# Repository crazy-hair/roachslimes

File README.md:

# roachslimes

This document is no longer being updated and will only be corrected on major updates! For full documentation please check out [The Docs](https://crazy-hair.github.io/roachslimes/)

A utilitarian tracker design for [SlimeVR](https://docs.slimevr.dev/), with the intention of using the cheapest parts available in the smallest form factor possible, while maintaining quality and usability.

## Ordering PCBs

**NEW!** Revision 2 motherboards have been added, removing the BMI160-QMC5883 IMU-Magnetometer combo, and replacing it with an [LSM6DSR](https://moffshop.deyta.de/products/lsm6dsr) board which has a magnetometer built in. Technically, the LSM6DSR board is pin-compatible with the BMI160 (and therefore is compatible with the old rev 1 boards), but this new design allows for much easier direct mounting (instead of using pin headers) and frees up space for a battery connector, instead of directly soldering the battery to the board. They're currently untested, still waiting for my batch to arrive, so use at your own risk!

The included gerbers in `/PCB/Production/` are exported from KiCad using the recommended settings for [JLCPCB](https://jlcpcb.com). I cannot guarantee that they will work at a different fab. JLCPCB is far and away the most cost effective for low volume PCB orders, coming out to $3.52 for 20 boards before tax if you use their economy shipping option (as of 2024). There are four files, two for each board (one single board, and one panelized). Using the panelized board files is highly recommended, as it allows for More Board Per Board<sup>TM</sup> without additional cost. The default JLCPCB order parameters are good enough for working boards out of the box, but I'd recommend changing the color to yellow [(because it's lemon scented)](https://x.com/MKVRiscy/status/1821870120697987492) and to select "no mark" so you don't have some unique identifier printed on the board somewhere.

## Ordering Parts

Links to all required components can be found in the table futher down.

## Printing Instructions

The print files, STLs, and Fusion source files are included in the `/3D Files/` directory. I highly recommend using the `.3mf` print files as a basis for your print, as there are manually painted supports and custom settings per object (there's one `.3mf` for PrusaSlicer and friends and one for OrcaSlicer and friends).

## Assembly

This board is designed to be compact, which means I had to make some unconventional choices during assembly. The D1 Mini and TP-4056 Boards are mounted to the surface of the PCB, while the BMI and QMC are mounted on headers on the opposite side. For assembly, this means you have to solder the headers on first, then use flush cutters or snips to cut the header pins sticking out of the front of the board down to be flush so you can solder on the boards on the onto the front. There's also a pogo pin header for a future modular charging dock which would allow for charging multiple trackers at once, and a slot for an LED and associated resistor which was added for debugging but can be used to identify trackers if you choose to use different colored LEDs per tracker. The cases are completely toolless and are friction/retention fit. Refer to the animation below for an assembly reference.

## Firmware

Firmware is pretty straightforward, though I did have an issue with the Butterscotch builder/installer - battery sense would always show 100 percent. Therefore, if you want all features to work, I'd recommend building it yourself - PlatformIO Tools for Visual Studio Code make it super easy. If you're compiling yourself, all you have to do is uncomment out `BATTERY_SHIELD_RESISTANCE 180` in `defines.h`, set `USE_6_AXIS false` in `debug.h`, and and change `BMI160_MAG_TYPE BMI160_MAG_TYPE_HMC` to `BMI160_MAG_TYPE BMI160_MAG_TYPE_QMC`in `defines_bmi160.h`. If that makes no sense to you, I've included compiled firmware in the releases section. 

## Price Breakdown

A fully parametric breakdown that allows for adjusting tax, quantity, and more can be found in BOM.xlsx or [here](https://docs.google.com/spreadsheets/d/1RTwIJsGUY1e1f047yFT5OwqJSmgT3SN4hO7gHYImR_g/copy) (if you want to modify it, you'll have to make a copy first).

All prices are in USD. Sales tax is calculated at 8.25%. The table is based on a full set of trackers and includes 2 extra D1s, BMIs, and QMCs to account for possible DOA parts or accidents during assembly. Note that the LED and associated 620Ω resistor, as well as the pogo pins are not necessary for core tracker operation, as specified in the comment row.

| Tracker Components | [D1 Mini v4](https://www.aliexpress.us/item/32831353752.html) | [BMI160](https://www.aliexpress.us/item/1005007143698152.html) | [TP-4056](https://www.aliexpress.us/item/1005006379403615.html) | [GY-271](https://www.aliexpress.us/item/1556804905.html) | [SK12D07VG4](https://www.aliexpress.us/item/3256806149664764.html) | [JST-PH-4P](https://www.aliexpress.us/item/33011797617.html) | [Pogo Female](https://www.aliexpress.us/item/3256804960956555.html) | [B5817WS](https://www.aliexpress.us/item/1005004633629467.html) | [0805 180k](https://www.aliexpress.us/item/1005007032369041.html) | [0806 620r](https://www.aliexpress.us/item/3256806846054289.html) | [0805 LED](https://www.aliexpress.us/item/3256805245629305.html) | [803450](https://www.aliexpress.us/item/1005003621836701.html) | [Wires](https://www.aliexpress.us/item/1005007558078161.html) | Motherboard | Daughterboard | Total |
| ------------------------------ | ---------------------------------------------------------- | -------------------------------------------------------------- | -------------------------------------------------------------- | -------------------------------------------------------- | ------------------------------------------------------------------ | ------------------------------------------------------------ | ------------------------------------------------------------------- | --------------------------------------------------------------- | ----------------------------------------------------------------- | ----------------------------------------------------------------- | ---------------------------------------------------------------- | -------------------------------------------------------------- | ------------------------------------------------------------- | ----------------------------- | --------------------------------- | ------------ |
| Listing Price | $1.43 | $0.88 | $3.27 | $0.58 | $1.20 | $3.79 | $12.93 | $1.20 | $1.05 | $1.05 | $2.47 | $25.99 | $11.93 | $2.00 | $2.00 | |
| Shipping | $2.63 | $2.32 | $ \- | $ \- | $ \- | $ \- | $ \- | $ \- | $ \- | $ \- | $ \- | $ \- | $ \- | $1.52 | $1.52 | $7.99 |
| Subtotal | $15.50 | $12.88 | $3.27 | $6.96 | $1.20 | $3.79 | $12.93 | $1.20 | $1.05 | $1.05 | $2.47 | $25.99 | $11.93 | $3.52 | $3.52 | $107.26 |
| Tax | $1.28 | $1.06 | $0.27 | $0.57 | $0.10 | $0.31 | $1.07 | $0.10 | $0.09 | $0.09 | $0.20 | $2.14 | $0.98 | $0.29 | $0.29 | $8.85 |
| Total | $16.78 | $13.94 | $3.54 | $7.53 | $1.30 | $4.10 | $14.00 | $1.30 | $1.14 | $1.14 | $2.67 | $28.13 | $12.91 | $3.81 | $3.81 | $116.11 |
| Order Quantity | 9 | 12 | 1 | 12 | 1 | 1 | 1 | 1 | 1 | 1 | 1 | 1 | 1 | 1 | 1 | |
| Item Quantity | 1 | 1 | 20 | 1 | 20 | 100 | 20 | 100 | 100 | 100 | 600 | 10 | 12 | 20 | 40 | |
| Price Per Unit | $1.86 | $1.16 | $0.18 | $0.63 | $0.06 | $0.04 | $0.70 | $0.01 | $0.01 | $0.01 | $0.00 | $2.81 | $1.08 | $0.19 | $0.10 | |
| | | | | | | | | | | | | | | | | |
| Quantity Per Primary Tracker | 1 | 1 | 1 | 1 | 1 | 1 | 1 | 2 | 1 | 1 | 1 | 1 | 0 | 1 | 0 | |
| Quantity Per Secondary Tracker | 0 | 1 | 0 | 1 | 0 | 1 | 0 | 0 | 0 | 0 | 0 | 0 | 1 | 0 | 1 | |
| | | | | | | | | | | | | | | | | |
| Price Per Primary Tracker | $1.86 | $1.16 | $0.18 | $0.63 | $0.06 | $0.04 | $0.70 | $0.03 | $0.01 | $0.01 | $0.00 | $2.81 | $ \- | $0.19 | $ \- | $7.69 |
| Price Per Secondary Tracker | $ \- | $1.16 | $ \- | $0.63 | $ \- | $0.04 | $ \- | $ \- | $ \- | $ \- | $ \- | $ \- | $1.08 | $ \- | $0.10 | $3.00 |
| | | | | | | | | | | | | | | | | |
| Comment | | | | | | | Optional | | | Optional | Optional | | | | | |

## Gallery

## Credits

List of models used:

| Model | Credit |
|--|--:|
| Wemos D1 Mini v4 | [FBMinis](https://grabcad.com/library/wemos-esp8266-lolin-d1-mini-v4-1) |
| TP-4056 | [Babu George](https://grabcad.com/library/03962a-hw107-lithium-battery-charging-module-1) |
| BMI160 | [Kouno](https://store.kouno.xyz/products/bmi270-breakout-board) |
| GY-271 | [Benas Griauzde](https://grabcad.com/library/gy-271-hmc5883l-triple-3-axis-digital-compass-magnetometer-sensor-module-1) |

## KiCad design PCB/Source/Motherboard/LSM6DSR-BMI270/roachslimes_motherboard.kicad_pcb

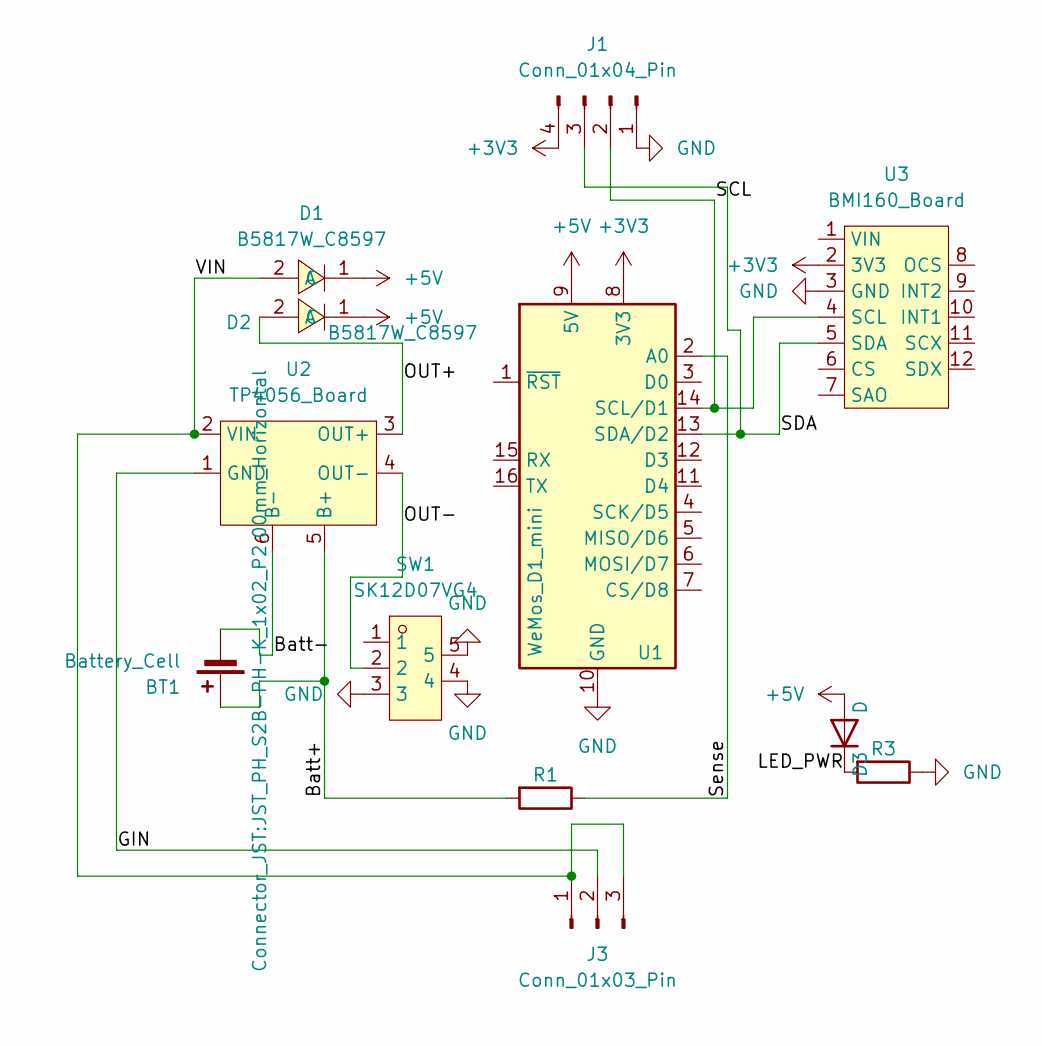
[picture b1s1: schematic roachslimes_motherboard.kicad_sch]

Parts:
BT1: Battery_Cell; JST_PH_S2B-PH-K_1x02_P2.00mm_Horizontal
D1, D2: B5817W_C8597; SOD-123_L2.8-W1.8-LS3.7-RD_custom; LCSC Part C8597
D3: D; LED_0805_2012Metric_Pad1.15x1.40mm_HandSolder
J1: Conn_01x04_Pin; JST_PH_S4B-PH-K_1x04_P2.00mm_Horizontal_labelled_1
J3: Conn_01x03_Pin; pogo_3_pin_right_angle
R1, R3: R; R_0805_2012Metric_Pad1.20x1.40mm_HandSolder
SW1: SK12D07VG4; SW-TH_SK12D07VG4_custom; LCSC Part C2887263
U1: WeMos_D1_mini; WEMOS_D1_mini_light_labeled_both_sides_1
U2: TP4056_Board; TP4056_both_sides_1
U3: BMI160_Board; LSM6DSR _Board

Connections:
+3V3: J1.4, U1.8 (3V3), U3.2 (3V3)
+5V: D1.1 (C), D2.1 (C), D3.2 (A), U1.9 (5V)
/Batt+: BT1.1 (+), R1.2, U2.5 (B+)
/Batt-: BT1.2 (-), U2.6 (B-)
/GIN: J3.2, U2.1 (GND)
/LED_PWR: D3.1 (K), R3.2
/OUT+: D2.2 (A), U2.3 (OUT+)
/OUT-: SW1.2, U2.4 (OUT-)
/SCL: J1.2, U1.14 (SCL/D1), U3.4 (SCL)
/SDA: J1.3, U1.13 (SDA/D2), U3.5 (SDA)
/Sense: R1.1, U1.2 (A0)
/VIN: D1.2 (A), J3.1, J3.3, U2.2 (VIN)
GND: J1.1, R3.1, SW1.3, SW1.4, SW1.5, U1.10 (GND), U3.3 (GND)

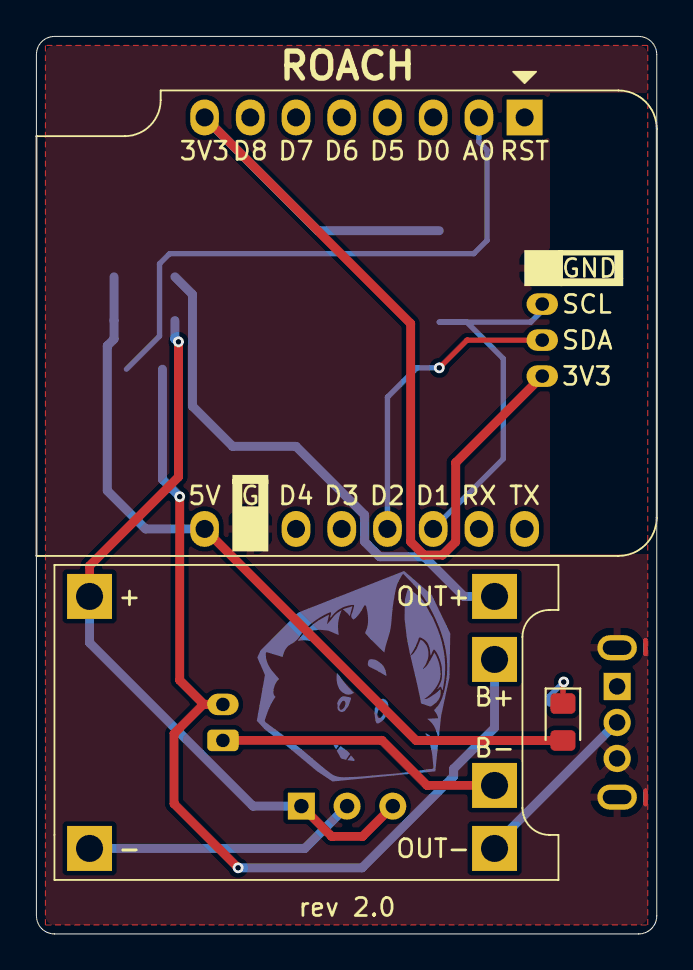
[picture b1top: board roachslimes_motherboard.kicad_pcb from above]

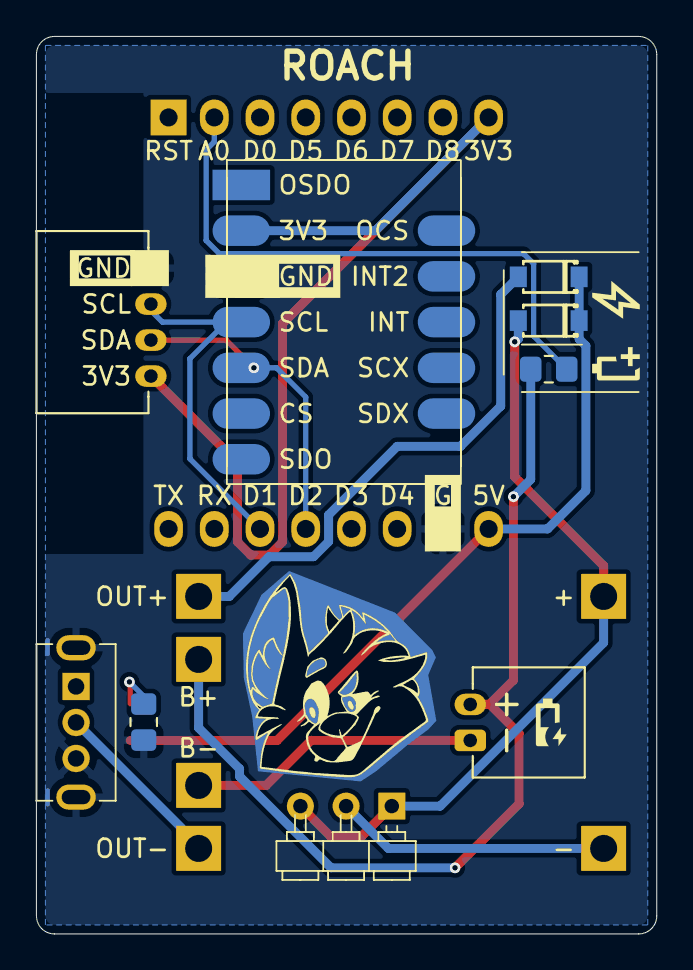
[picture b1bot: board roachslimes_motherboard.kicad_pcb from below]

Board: 2 copper layers, 34.5 x 49.9 mm, 12 parts (9 on the bottom side), 13 nets.

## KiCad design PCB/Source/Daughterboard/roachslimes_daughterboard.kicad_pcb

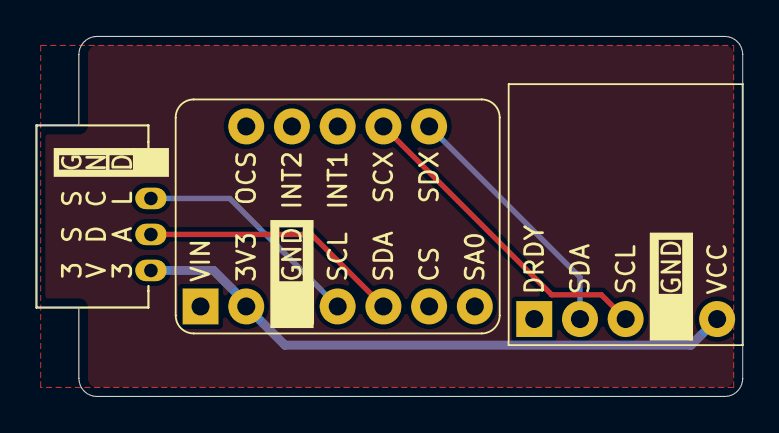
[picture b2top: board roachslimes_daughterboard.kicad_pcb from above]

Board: 2 copper layers, 39.2 x 20.0 mm, 3 parts (0 on the bottom side), 6 nets.

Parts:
J1: JST PH 4p; JST_PH_1x4_labelled
U1: BMI160; BMI160_Board_both_sides_1
U2: GY-271; GY-271_both_sides_1

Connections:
+3V3: J1.4, U1.2 (3V3), U2.5 (VCC)
/SCL: J1.2, U1.4 (SCL)
/SCX: U1.11 (SCX), U2.3 (SCL)
/SDA: J1.3, U1.5 (SDA)
/SDX: U1.12 (SDX), U2.2 (SDA)
GND: J1.1, U1.3 (GND), U2.4 (GND)

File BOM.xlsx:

Tracker Components | D1 Mini | BMI160 | TP4056 | GY-271 | SK12D07VG4 | JST-PH-4P | Pogo Female | B5817WS | 0805 180k | 0806 620r | 0805 LED | 803450 | Wires | Motherboard | Daughterboard | Total
Listing Price | 1.43 | 0.88 | 3.27 | 0.57999999999999996 | 1.2 | 3.79 | 12.93 | 1.2 | 1.05 | 1.05 | 2.4700000000000002 | 25.99 | 11.93 | 2 | 2
Shipping | 2.63 | 2.3199999999999998 | 0 | 0 | 0 | 0 | 0 | 0 | 0 | 0 | 0 | 0 | 0 | 1.52 | 1.52 | 7.9899999999999984
Subtotal | 15.5 | 12.88 | 3.27 | 6.9599999999999991 | 1.2 | 3.79 | 12.93 | 1.2 | 1.05 | 1.05 | 2.4700000000000002 | 25.99 | 11.93 | 3.52 | 3.52 | 107.25999999999999 |  | Tax Rate
Tax | 1.2787500000000001 | 1.0626000000000002 | 0.26977499999999999 | 0.57419999999999993 | 9.9000000000000005E-2 | 0.31267500000000004 | 1.0667249999999999 | 9.9000000000000005E-2 | 8.6625000000000008E-2 | 8.6625000000000008E-2 | 0.20377500000000004 | 2.1441750000000002 | 0.98422500000000002 | 0.29039999999999999 | 0.29039999999999999 | 8.8489500000000003 |  | 8.2500000000000004E-2
Total | 16.778749999999999 | 13.942600000000001 | 3.5397750000000001 | 7.5341999999999993 | 1.2989999999999999 | 4.1026749999999996 | 13.996725 | 1.2989999999999999 | 1.136625 | 1.136625 | 2.673775 | 28.134174999999999 | 12.914225 | 3.8104 | 3.8104 | 116.10895000000001
Order Quantity | 9 | 12 | 1 | 12 | 1 | 1 | 1 | 1 | 1 | 1 | 1 | 1 | 1 | 1 | 1 |  |  | Materials Cost | Lower Body Set | Core Set | Enhanced Core Set | Full Body Set | Deluxe Tracker Set
Item Quantity | 1 | 1 | 20 | 1 | 20 | 100 | 20 | 100 | 100 | 100 | 600 | 10 | 12 | 20 | 40 |  |  | Primary Tracker Quantity | 5 | 5 | 5 | 7 | 10
Price Per Unit | 1.8643055555555554 | 1.1618833333333334 | 0.17698875 | 0.62784999999999991 | 6.4949999999999994E-2 | 4.1026749999999994E-2 | 0.69983624999999994 | 1.299E-2 | 1.136625E-2 | 1.136625E-2 | 4.4562916666666666E-3 | 2.8134174999999999 | 1.0761854166666667 | 0.19051999999999999 | 9.5259999999999997E-2 |  |  | Secondary Tracker Quantity | 0 | 1 | 3 | 3 | 6 |  | Assembly Time Per Primary Tracker | 33
 |  |  |  |  |  |  |  |  |  |  |  |  |  |  |  |  |  |  |  |  |  |  |  |  | Assembly Time Per Secondary Tracker | 5
Quantity Per Primary Tracker | 1 | 1 | 1 | 1 | 1 | 1 | 1 | 2 | 1 | 1 | 1 | 1 | 0 | 1 | 0 |  |  | 500mm Strap Quantity | 6 | 8 | 8 | 10 | 10 |  | Assembly Time Per Charging Dock | 30
Quantity Per Secondary Tracker | 0 | 1 | 0 | 1 | 0 | 1 | 0 | 0 | 0 | 0 | 0 | 0 | 1 | 0 | 1 |  |  | 300mm Strap Quantity | 0 | 0 | 2 | 2 | 2
 |  |  |  |  |  |  |  |  |  |  |  |  |  |  |  |  |  |  |  |  |  |  |  |  | Hourly Wage | 22
Price Per Primary Tracker | 1.8643055555555554 | 1.1618833333333334 | 0.17698875 | 0.62784999999999991 | 6.4949999999999994E-2 | 4.1026749999999994E-2 | 0.69983624999999994 | 2.598E-2 | 1.136625E-2 | 1.136625E-2 | 4.4562916666666666E-3 | 2.8134174999999999 | 0 | 0.19051999999999999 | 0 | 7.6939469305555557 |  | Price of Primary Trackers | 38.469734652777781 | 38.469734652777781 | 38.469734652777781 | 53.857628513888891 | 76.939469305555562
Price Per Secondary Tracker | 0 | 1.1618833333333334 | 0 | 0.62784999999999991 | 0 | 4.1026749999999994E-2 | 0 | 0 | 0 | 0 | 0 | 0 | 1.0761854166666667 | 0 | 9.5259999999999997E-2 | 3.0022055000000001 |  | Price of Secondary Trackers | 0 | 3.0022055000000001 | 9.0066164999999998 | 9.0066164999999998 | 18.013233
Comment |  |  |  |  |  |  | Optional |  |  | Optional | Optional |  |  |  |  |  |  | Price of 500mm Straps | 4.7803199999999997 | 6.3737599999999999 | 6.3737599999999999 | 7.9672000000000001 | 7.9672000000000001
 |  |  |  |  |  |  |  |  |  |  |  |  |  |  |  |  |  | Price of 300mm Straps | 0 | 0 | 1.32498 | 1.32498 | 1.32498
Ancillary Components | 38x300mm Strap | 38x500mm Strap | Chest Harness
Listing Price | 3.06 | 3.68 | 8.0500000000000007 |  |  |  |  |  |  |  |  |  |  |  |  |  |  | Total Price of Set | 43.250054652777777 | 47.845700152777781 | 55.175091152777782 | 72.156425013888892 | 104.24488230555556
Shipping | 0 | 0 | 0
Subtotal | 6.12 | 7.36 | 8.0500000000000007 |  |  |  |  |  |  |  |  |  |  |  |  |  |  | Assembly Cost | Lower Body Set | Core Set | Enhanced Core Set | Full Body Set | Deluxe Tracker Set
Tax | 0.50490000000000002 | 0.60720000000000007 | 0.66412500000000008 |  |  |  |  |  |  |  |  |  |  |  |  |  |  | Total Price of Primary Assembly | 60.5 | 60.5 | 60.5 | 84.7 | 121
Total | 6.6249000000000002 | 7.9672000000000001 | 8.714125000000001 |  |  |  |  |  |  |  |  |  |  |  |  |  |  | Total Price of Secondary Assembly | 0 | 1.8333333333333333 | 5.5 | 5.5 | 11
Order Quantity | 2 | 2 | 1 |  |  |  |  |  |  |  |  |  |  |  |  |  |  | Total Price of Assembly | 60.5 | 62.333333333333336 | 66 | 90.2 | 132
Item Quantity | 5 | 5 | 1
Price Per Unit | 0.66249000000000002 | 0.79671999999999998 | 8.714125000000001 |  |  |  |  |  |  |  |  |  |  |  |  |  |  | Total Price of Assembled Set | 103.75005465277778 | 110.17903348611111 | 121.17509115277778 | 162.3564250138889 | 236.24488230555556
Comment |  |  | Optional |  |  |  |  |  |  |  |  |  |  |  |  |  |  | Optional Addons | Lower Body Set | Core Set | Enhanced Core Set | Full Body Set | Deluxe Tracker Set
 |  |  |  |  |  |  |  |  |  |  |  |  |  |  |  |  | 0 | Chest Harness | 0 | 0 | 0 | 0 | 0
Charging Dock Components | Pogo Male | USB-C Female SMD | PCB | Total |  |  |  |  |  |  |  |  |  |  |  |  | 0 | Charging Dock | 0 | 0 | 0 | 0 | 0
Listing Price | 2.83 | 1.43 | 2 | 6.26 |  |  |  |  |  |  |  |  |  |  |  |  | 0 | Identity LEDs | 0 | 0 | 0 | 0 | 0
Shipping | 0 | 0 | 1.52 | 1.52 |  |  |  |  |  |  |  |  |  |  |  |  | 1 | 3D Printed Motherboard Cases | 8.4499999999999993 | 8.4499999999999993 | 8.4499999999999993 | 11.83 | 16.899999999999999
Subtotal | 11.32 | 1.43 | 3.52 | 16.27 |  |  |  |  |  |  |  |  |  |  |  |  | 1 | 3D Printed Daughterboard Cases | 0 | 0.83 | 2.4899999999999998 | 2.4899999999999998 | 4.9799999999999995
Tax | 0.93390000000000006 | 0.117975 | 0.29039999999999999 | 1.3422750000000001
Total | 12.2539 | 1.5479749999999999 | 3.8104 | 17.612275 |  |  |  |  |  |  |  |  |  |  |  |  |  | Total Price of Addons | 8.4499999999999993 | 9.2799999999999994 | 10.94 | 14.32 | 21.88
Order Quantity | 4 | 1 | 1
Item Quantity | 5 | 10 | 5 |  |  |  |  |  |  |  |  |  |  |  |  |  |  | Total Price | 112.20005465277778 | 119.45903348611111 | 132.11509115277778 | 176.67642501388889 | 258.12488230555556
Price Per Unit | 0.61269499999999999 | 0.15479749999999998 | 0.76207999999999998
Quantity Per Dock | 8 | 1 | 2
 |  |  |  |  |  | Assembled Price
Price Per Dock | 4.9015599999999999 | 0.15479749999999998 | 1.52416 | 6.5805175 |  | 18.680517500000001
Comment

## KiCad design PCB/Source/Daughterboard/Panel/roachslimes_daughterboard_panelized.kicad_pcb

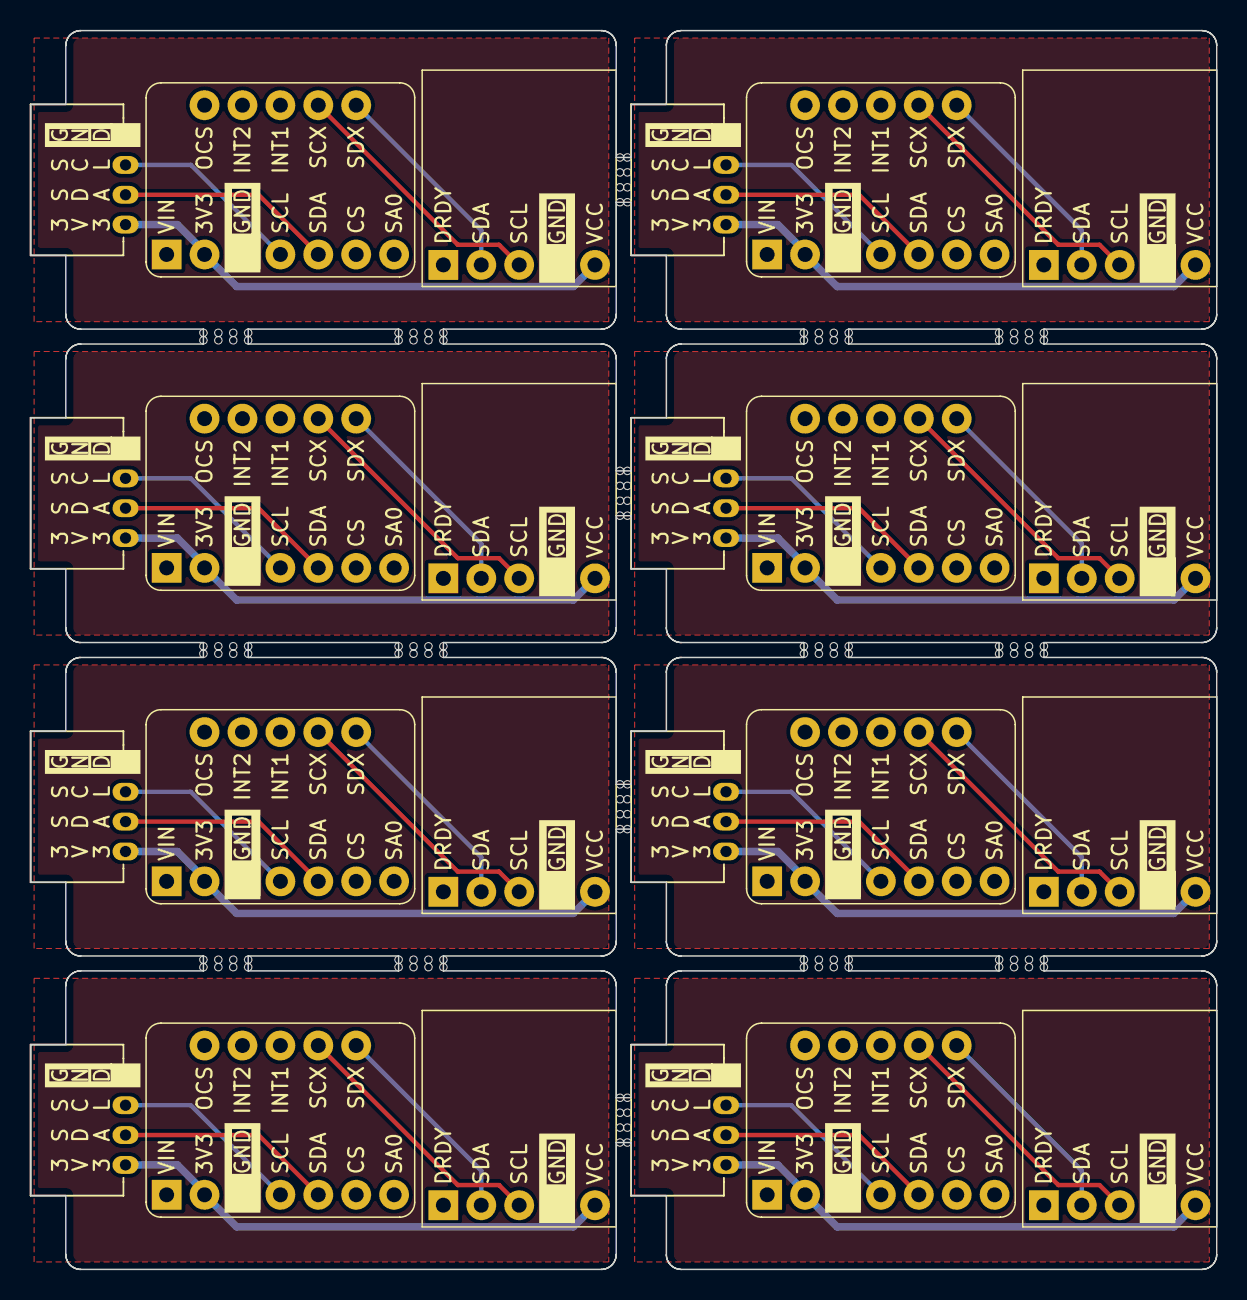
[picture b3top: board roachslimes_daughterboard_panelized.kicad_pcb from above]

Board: 2 copper layers, 79.5 x 83.0 mm, 152 parts (0 on the bottom side), 48 nets.

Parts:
J1, J1#2, J1#3, J1#4, J1#5, J1#6, J1#7, J1#8: JST PH 4p; JST_PH_1x4_labelled
KiKit_MB_1_1, KiKit_MB_1_2, KiKit_MB_1_3, KiKit_MB_1_4, KiKit_MB_2_1, KiKit_MB_2_2, KiKit_MB_2_3, KiKit_MB_2_4, KiKit_MB_3_1, KiKit_MB_3_2, KiKit_MB_3_3, KiKit_MB_3_4, KiKit_MB_4_1, KiKit_MB_4_2, KiKit_MB_4_3, KiKit_MB_4_4, KiKit_MB_5_1, KiKit_MB_5_2, KiKit_MB_5_3, KiKit_MB_5_4, KiKit_MB_6_1, KiKit_MB_6_2, KiKit_MB_6_3, KiKit_MB_6_4, KiKit_MB_7_1, KiKit_MB_7_2, KiKit_MB_7_3, KiKit_MB_7_4, KiKit_MB_8_1, KiKit_MB_8_2, KiKit_MB_8_3, KiKit_MB_8_4, KiKit_MB_9_1, KiKit_MB_9_2, KiKit_MB_9_3, KiKit_MB_9_4, KiKit_MB_10_1, KiKit_MB_10_2, KiKit_MB_10_3, KiKit_MB_10_4, KiKit_MB_11_1, KiKit_MB_11_2, KiKit_MB_11_3, KiKit_MB_11_4, KiKit_MB_12_1, KiKit_MB_12_2, KiKit_MB_12_3, KiKit_MB_12_4, KiKit_MB_13_1, KiKit_MB_13_2, KiKit_MB_13_3, KiKit_MB_13_4, KiKit_MB_14_1, KiKit_MB_14_2, KiKit_MB_14_3, KiKit_MB_14_4, KiKit_MB_15_1, KiKit_MB_15_2, KiKit_MB_15_3, KiKit_MB_15_4, KiKit_MB_16_1, KiKit_MB_16_2, KiKit_MB_16_3, KiKit_MB_16_4, KiKit_MB_17_1, KiKit_MB_17_2, KiKit_MB_17_3, KiKit_MB_17_4, KiKit_MB_18_1, KiKit_MB_18_2, KiKit_MB_18_3, KiKit_MB_18_4, KiKit_MB_19_1, KiKit_MB_19_2, KiKit_MB_19_3, KiKit_MB_19_4, KiKit_MB_20_1, KiKit_MB_20_2, KiKit_MB_20_3, KiKit_MB_20_4, KiKit_MB_21_1, KiKit_MB_21_2, KiKit_MB_21_3, KiKit_MB_21_4, KiKit_MB_22_1, KiKit_MB_22_2, KiKit_MB_22_3, KiKit_MB_22_4, KiKit_MB_23_1, KiKit_MB_23_2, KiKit_MB_23_3, KiKit_MB_23_4, KiKit_MB_24_1, KiKit_MB_24_2, KiKit_MB_24_3, KiKit_MB_24_4, KiKit_MB_25_1, KiKit_MB_25_2, KiKit_MB_25_3, KiKit_MB_25_4, KiKit_MB_26_1, KiKit_MB_26_2, KiKit_MB_26_3, KiKit_MB_26_4, KiKit_MB_27_1, KiKit_MB_27_2, KiKit_MB_27_3, KiKit_MB_27_4, KiKit_MB_28_1, KiKit_MB_28_2, KiKit_MB_28_3, KiKit_MB_28_4, KiKit_MB_29_1, KiKit_MB_29_2, KiKit_MB_29_3, KiKit_MB_29_4, KiKit_MB_30_1, KiKit_MB_30_2, KiKit_MB_30_3, KiKit_MB_30_4, KiKit_MB_31_1, KiKit_MB_31_2, KiKit_MB_31_3, KiKit_MB_31_4, KiKit_MB_32_1, KiKit_MB_32_2, KiKit_MB_32_3, KiKit_MB_32_4: NPTH
U1, U1#2, U1#3, U1#4, U1#5, U1#6, U1#7, U1#8: BMI160; BMI160_Board_both_sides_1
U2, U2#2, U2#3, U2#4, U2#5, U2#6, U2#7, U2#8: GY-271; GY-271_both_sides_1

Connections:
Board_0-+3V3: J1#5.4, U1#7.2 (3V3), U2#7.5 (VCC)
Board_0-/SCL: J1#5.2, U1#7.4 (SCL)
Board_0-/SCX: U1#7.11 (SCX), U2#7.3 (SCL)
Board_0-/SDA: J1#5.3, U1#7.5 (SDA)
Board_0-/SDX: U1#7.12 (SDX), U2#7.2 (SDA)
Board_0-GND: J1#5.1, U1#7.3 (GND), U2#7.4 (GND)
Board_1-+3V3: J1#4.4, U1#3.2 (3V3), U2.5 (VCC)
Board_1-/SCL: J1#4.2, U1#3.4 (SCL)
Board_1-/SCX: U1#3.11 (SCX), U2.3 (SCL)
Board_1-/SDA: J1#4.3, U1#3.5 (SDA)
Board_1-/SDX: U1#3.12 (SDX), U2.2 (SDA)
Board_1-GND: J1#4.1, U1#3.3 (GND), U2.4 (GND)
Board_2-+3V3: J1#7.4, U1#6.2 (3V3), U2#8.5 (VCC)
Board_2-/SCL: J1#7.2, U1#6.4 (SCL)
Board_2-/SCX: U1#6.11 (SCX), U2#8.3 (SCL)
Board_2-/SDA: J1#7.3, U1#6.5 (SDA)
Board_2-/SDX: U1#6.12 (SDX), U2#8.2 (SDA)
Board_2-GND: J1#7.1, U1#6.3 (GND), U2#8.4 (GND)
Board_3-+3V3: J1#3.4, U1.2 (3V3), U2#4.5 (VCC)
Board_3-/SCL: J1#3.2, U1.4 (SCL)
Board_3-/SCX: U1.11 (SCX), U2#4.3 (SCL)
Board_3-/SDA: J1#3.3, U1.5 (SDA)
Board_3-/SDX: U1.12 (SDX), U2#4.2 (SDA)
Board_3-GND: J1#3.1, U1.3 (GND), U2#4.4 (GND)
Board_4-+3V3: J1.4, U1#5.2 (3V3), U2#6.5 (VCC)
Board_4-/SCL: J1.2, U1#5.4 (SCL)
Board_4-/SCX: U1#5.11 (SCX), U2#6.3 (SCL)
Board_4-/SDA: J1.3, U1#5.5 (SDA)
Board_4-/SDX: U1#5.12 (SDX), U2#6.2 (SDA)
Board_4-GND: J1.1, U1#5.3 (GND), U2#6.4 (GND)
Board_5-+3V3: J1#2.4, U1#4.2 (3V3), U2#3.5 (VCC)
Board_5-/SCL: J1#2.2, U1#4.4 (SCL)
Board_5-/SCX: U1#4.11 (SCX), U2#3.3 (SCL)
Board_5-/SDA: J1#2.3, U1#4.5 (SDA)
Board_5-/SDX: U1#4.12 (SDX), U2#3.2 (SDA)
Board_5-GND: J1#2.1, U1#4.3 (GND), U2#3.4 (GND)
Board_6-+3V3: J1#8.4, U1#2.2 (3V3), U2#2.5 (VCC)
Board_6-/SCL: J1#8.2, U1#2.4 (SCL)
Board_6-/SCX: U1#2.11 (SCX), U2#2.3 (SCL)
Board_6-/SDA: J1#8.3, U1#2.5 (SDA)
Board_6-/SDX: U1#2.12 (SDX), U2#2.2 (SDA)
Board_6-GND: J1#8.1, U1#2.3 (GND), U2#2.4 (GND)
Board_7-+3V3: J1#6.4, U1#8.2 (3V3), U2#5.5 (VCC)
Board_7-/SCL: J1#6.2, U1#8.4 (SCL)
Board_7-/SCX: U1#8.11 (SCX), U2#5.3 (SCL)
Board_7-/SDA: J1#6.3, U1#8.5 (SDA)
Board_7-/SDX: U1#8.12 (SDX), U2#5.2 (SDA)
Board_7-GND: J1#6.1, U1#8.3 (GND), U2#5.4 (GND)

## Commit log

2024-10-07 Update LICENSE
    change to CC-BY-SA-4.0
2024-10-07 Update README.md
    add price table
2024-10-07 added motherboard project files
2024-10-07 add motherboard production files
2024-10-07 added motherboard panel
2024-10-07 add daughterboard and flush out readme
2024-10-07 flush out readme
2024-10-07 flesh out readme more
2024-10-07 remove extra files
2024-10-07 add Ordering Parts part of readme
2024-10-07 add disclaimer
2024-10-07 remove background from images
2024-10-07 fix images for readme
2024-10-07 fix images in readme
2024-10-07 add USD disclaimer
2024-10-07 add sales tax disclaimer
2024-10-07 fix minor spelling issues
2024-10-07 add BOM and adjust readme
2024-10-07 add google sheets link
2024-10-07 add firmware section to readme
2024-10-07 clarify resistor
2024-10-08 add addtional compile data and fix typo
2024-10-08 change table formatting
2024-10-08 add extra parts disclaimer
2024-10-08 update BOM link
2024-10-08 add stl to readme
2024-10-08 remove stl from readme
2024-10-08 update gitignore
2024-10-08 Delete PCB/Source/Motherboard/roachslimes_motherboard.round-tracks-config
    delete round tracks fonfig
2024-10-09 add assembly animation
2024-10-09 upload assembly animation
2024-10-09 update gif for efficiency
2024-10-09 re-render assembly gif
2024-10-09 update assembly gif
2024-10-09 misc readme changes
2024-10-09 add transparent bg to gif
2024-10-09 fix animation of assembly gif
2024-10-10 fix silkscreen in gif
2024-10-10 update assembly animation
2024-10-10 add credits
2024-10-11 add 3d models, update board renders
2024-10-13 add actual pictures to gallery
2024-10-14 added r1 case files
2024-10-14 add 3mf file
2024-10-14 add clarification for table
2024-10-14 update BOM to reflect price of cases
2024-10-14 add dabo plug
2024-10-14 add fusion source files
2024-10-14 update case design
2024-10-15 make loop holes bigger (and add orcaslicer file)
2024-10-15 update slicer files to reflect case changes
2024-10-16 update case locking mech
2024-10-16 update 3mf commentary
2024-10-19 finalize case designs, misc edits to readme
2024-10-20 upload glTFs
2024-10-20 change index to readme
2024-10-20 add video to website
2024-10-20 change theme to minima dark
2024-10-20 change markdown processor
2024-10-20 fix video paht
2024-10-20 change video background
2024-10-20 change theme to Primer
2024-10-20 change theme to chirpy
2024-10-20 update theme
2024-10-20 change theme to dark
2024-10-20 add assembly.md
2024-10-20 update background of video
2024-10-20 rename md files
2024-10-20 index.md
2024-10-20 update pages
2024-10-20 test seperate pages
2024-10-20 break out readme into jekyll pages
2024-10-20 fix title of printing instructions
2024-10-20 add aux link
2024-10-20 test gltf
2024-10-20 update background for speen
2024-10-20 rename speen
2024-10-20 update background for bouncyvids
2024-10-20 update backround for mobo bouncy
2024-10-20 attempt to embed gltf
2024-10-20 attempt 2 at gltf
2024-10-20 update speen background
2024-10-20 remove iframe
2024-10-20 change size of floaters
2024-10-20 update size of floaters
2024-10-20 update floatybouncy
2024-10-20 update index
2024-10-20 fix floatybouncy
2024-10-20 fix grammar error assembly
2024-10-20 add documentation disclaimer
2024-10-20 fix gallery, add 3d print pictures
2024-10-20 update gallery with vids
2024-10-20 update size of videos on gallery page
2024-10-20 Update index.md typo
2024-10-21 make slicer backgrounds transparent
2024-10-21 embed marmoset test
2024-10-21 make mview conform to iframe and add dabo
2024-10-21 update mviews
2024-10-21 update dabo mview typo
2024-10-21 fix mviews again
2024-10-21 update iframe size
2024-10-24 upload v2 cases, update assembly page, add disclaimer to readme
2024-10-24 update video width
2024-10-24 update video height
2024-10-24 fix assembly vid
2024-10-24 update floatybouncy vid
2024-10-24 update front page video width
2024-10-28 update model viewer test
2024-10-28 fix viewer html source glb path
2024-10-28 update modelviewers
2024-10-28 update model scale
2025-01-06 Update assembly.md
    Test video adaptive width
2025-01-11 Update assembly.md
    test scaling css
2025-01-11 video resize test
2025-01-11 adjust width of content in index.md
2025-01-11 test scale ifram index.md
2025-01-11 iframe size test
2025-01-11 iframe test size
2025-01-11 iframe resize test
2025-01-11 make all videos and iframes scale properly
2025-04-26 update credits
2025-05-02 Create CNAME
2025-05-03 fix grammatical issue
2025-05-05 add favico
2025-05-05 change favico.png
2025-05-05 Rename favico.png to favicon.png
2025-05-05 add favicon
2025-05-06 attempt to make page wider
2025-05-06 fix config
2025-05-06 attempt to widen webpage 2
2025-05-06 remove wider scss
2025-05-06 remove asset scss
2025-05-06 widening attempt no3
2025-05-06 widening attempt 4
2025-05-06 wide attempt 5
2025-05-06 again
2025-05-06 i have decided to indefinitely postpone the endevour of making the website content wider
2025-08-22 updated v2 case design, added more gallery pictures, and added some more manufacturing files for different printers.
2025-08-22 removed the videos from the gallery page because they decided to disobey the page structure for some reason
2025-09-02 added rev 2, which is designed around the LSM6DSR.
2025-09-02 add small notice about new revision to documentation
2025-09-03 update dabo_door stl
2025-09-04 redo gallery with new images
2025-09-04 remove release link
2025-09-04 restructure gallery with HTML
2025-09-04 fix HTML formatting
2025-09-04 clean up HTML more
2025-09-04 fix HTML for real?
2025-09-04 update PCB images
2025-09-04 fix webp files and remove unused images
2025-09-04 update landing page
2025-09-04 update 3d print production files
